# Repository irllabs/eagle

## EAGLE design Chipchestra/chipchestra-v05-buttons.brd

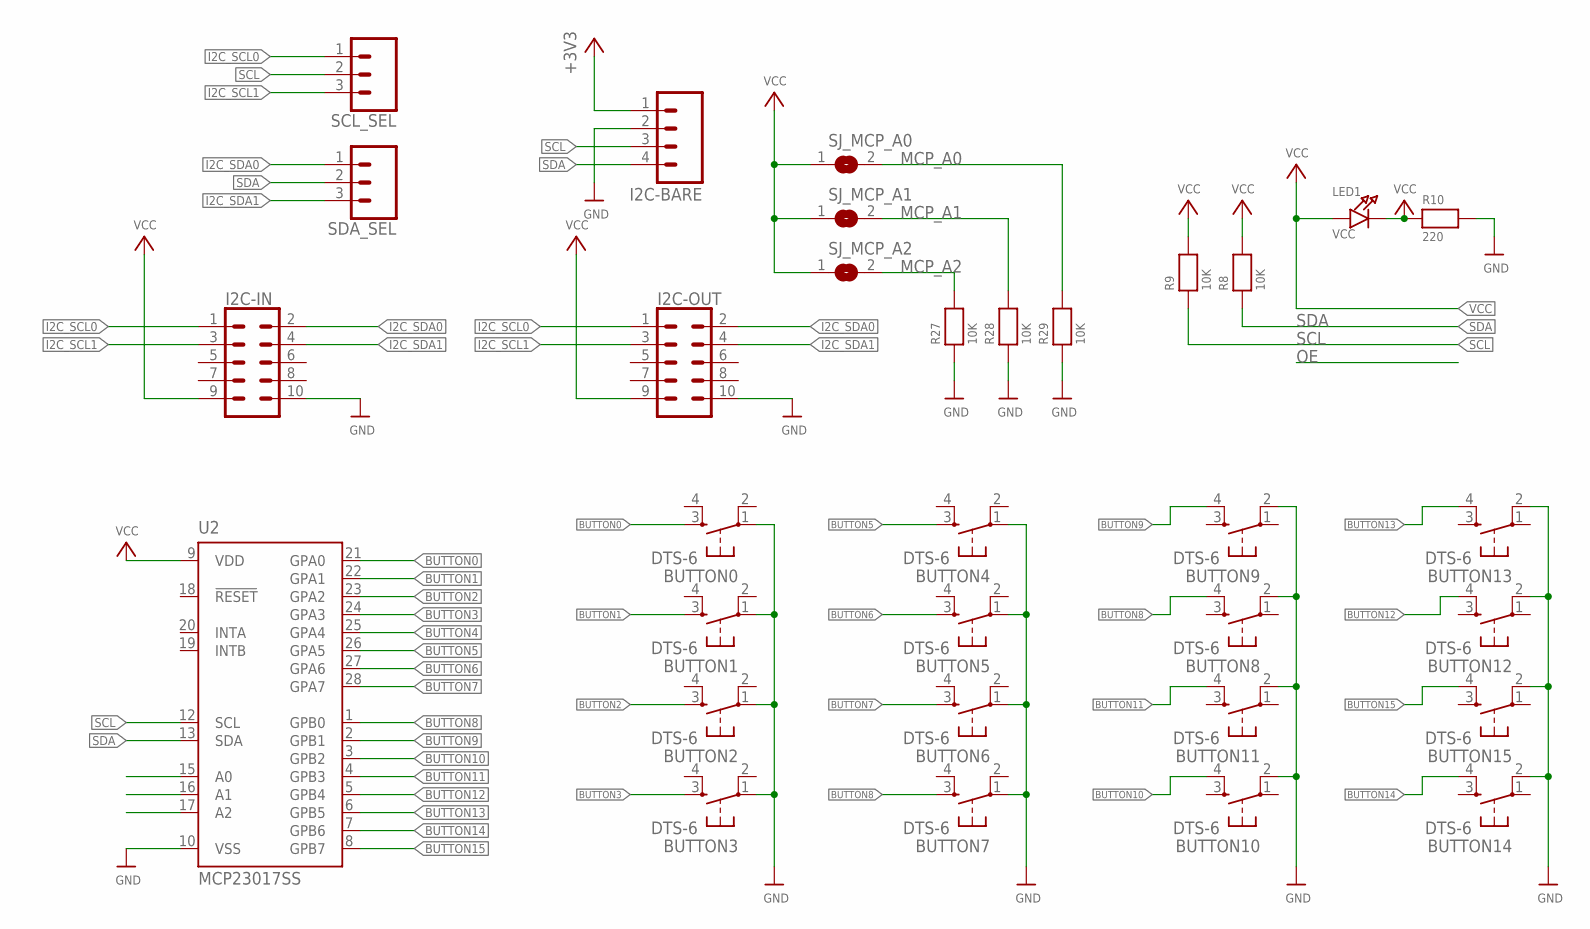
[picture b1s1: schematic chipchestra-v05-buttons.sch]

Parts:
BUTTON0, BUTTON1, BUTTON2, BUTTON3, BUTTON4, BUTTON5, BUTTON6, BUTTON7, BUTTON8, BUTTON9, BUTTON10, BUTTON11, BUTTON12, BUTTON13, BUTTON14, BUTTON15: DTS-6
I2C-BARE: M04LOCK; 1X04_LOCK
I2C-IN, I2C-OUT: CONN_05X2SHD_LOCK; 2X5-SHROUDED_LOCK
LED1: VCC; CHIPLED_0805
R8, R9, R27, R28, R29: 10K; 0805
R10: 220; 0805
SCL_SEL: CONN_03LOCK; 1X03_LOCK
SDA_SEL: CONN_03LOCK; 1X03_LOCK
SJ_MCP_A0, SJ_MCP_A1, SJ_MCP_A2: SOLDERJUMPERREFLOW_NOPASTE; SOLDERJUMPER_REFLOW_NOPASTE
U2: MCP23017SS; SSOP28

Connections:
+3V3: I2C-BARE.1
BUTTON0: BUTTON0.3, U2.21 (GPA0)
BUTTON1: BUTTON1.3, U2.22 (GPA1)
BUTTON2: BUTTON2.3, U2.23 (GPA2)
BUTTON3: BUTTON3.3, U2.24 (GPA3)
BUTTON4: U2.25 (GPA4)
BUTTON5: BUTTON4.3, U2.26 (GPA5)
BUTTON6: BUTTON5.3, U2.27 (GPA6)
BUTTON7: BUTTON6.3, U2.28 (GPA7)
BUTTON8: BUTTON7.3, BUTTON8.4, U2.1 (GPB0)
BUTTON9: BUTTON9.4, U2.2 (GPB1)
BUTTON10: BUTTON10.4, U2.3 (GPB2)
BUTTON11: BUTTON11.4, U2.4 (GPB3)
BUTTON12: BUTTON12.4, U2.5 (GPB4)
BUTTON13: BUTTON13.4, U2.6 (GPB5)
BUTTON14: BUTTON14.4, U2.7 (GPB6)
BUTTON15: BUTTON15.4, U2.8 (GPB7)
GND: BUTTON0.1, BUTTON1.1, BUTTON2.1, BUTTON3.1, BUTTON4.1, BUTTON5.1, BUTTON6.1, BUTTON7.1, BUTTON8.2, BUTTON9.2, BUTTON10.2, BUTTON11.2, BUTTON12.2, BUTTON13.2, BUTTON14.2, BUTTON15.2, I2C-BARE.2, I2C-IN.10, I2C-OUT.10, R10.2, R27.1, R28.1, R29.1, U2.10 (VSS)
I2C_SCL0: I2C-IN.1, I2C-OUT.1, SCL_SEL.1
I2C_SCL1: I2C-IN.3, I2C-OUT.3, SCL_SEL.3
I2C_SDA0: I2C-IN.2, I2C-OUT.2, SDA_SEL.1
I2C_SDA1: I2C-IN.4, I2C-OUT.4, SDA_SEL.3
MCP_A0: R29.2, SJ_MCP_A0.2, U2.15 (A0)
MCP_A1: R28.2, SJ_MCP_A1.2, U2.16 (A1)
MCP_A2: R27.2, SJ_MCP_A2.2, U2.17 (A2)
unnamed: LED1.C, R10.1
SCL: I2C-BARE.3, R9.1, SCL_SEL.2, U2.12 (SCL)
SDA: I2C-BARE.4, R8.1, SDA_SEL.2, U2.13 (SDA)
VCC: I2C-IN.9, I2C-OUT.9, LED1.A, R8.2, R9.2, SJ_MCP_A0.1, SJ_MCP_A1.1, SJ_MCP_A2.1, U2.9 (VDD)

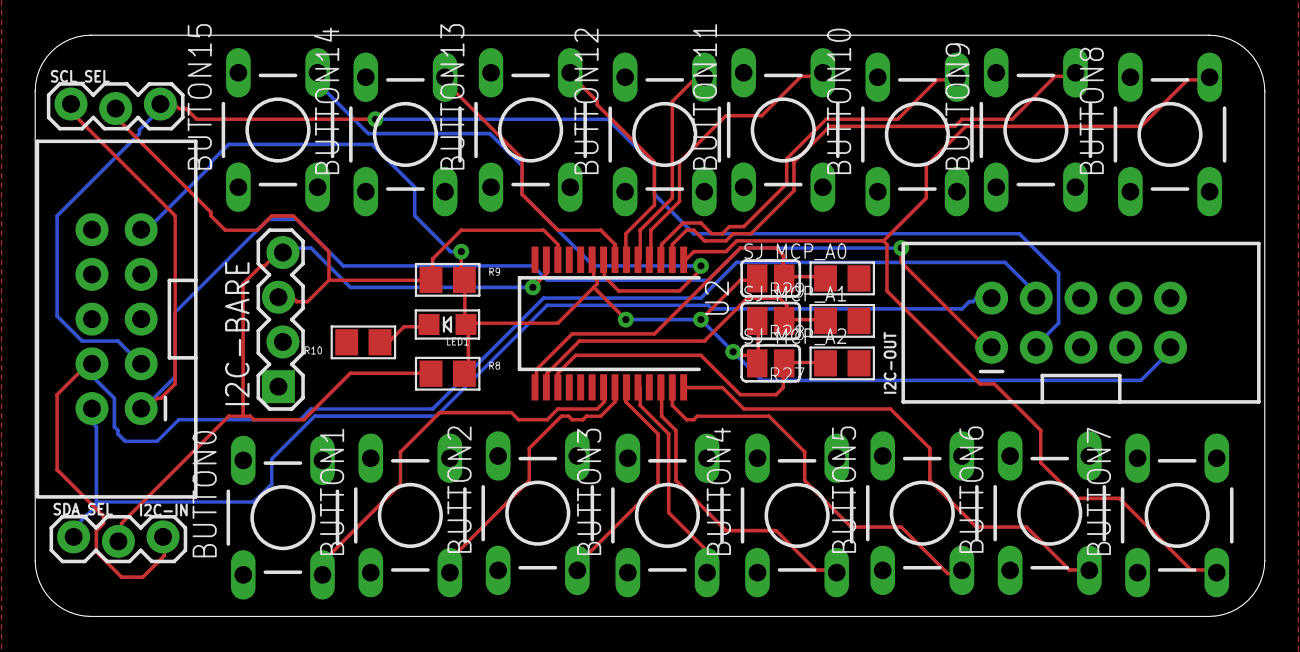
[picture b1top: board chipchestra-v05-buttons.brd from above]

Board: 2 copper layers, 69.8 x 33.0 mm, 32 parts (0 on the bottom side), 27 nets.

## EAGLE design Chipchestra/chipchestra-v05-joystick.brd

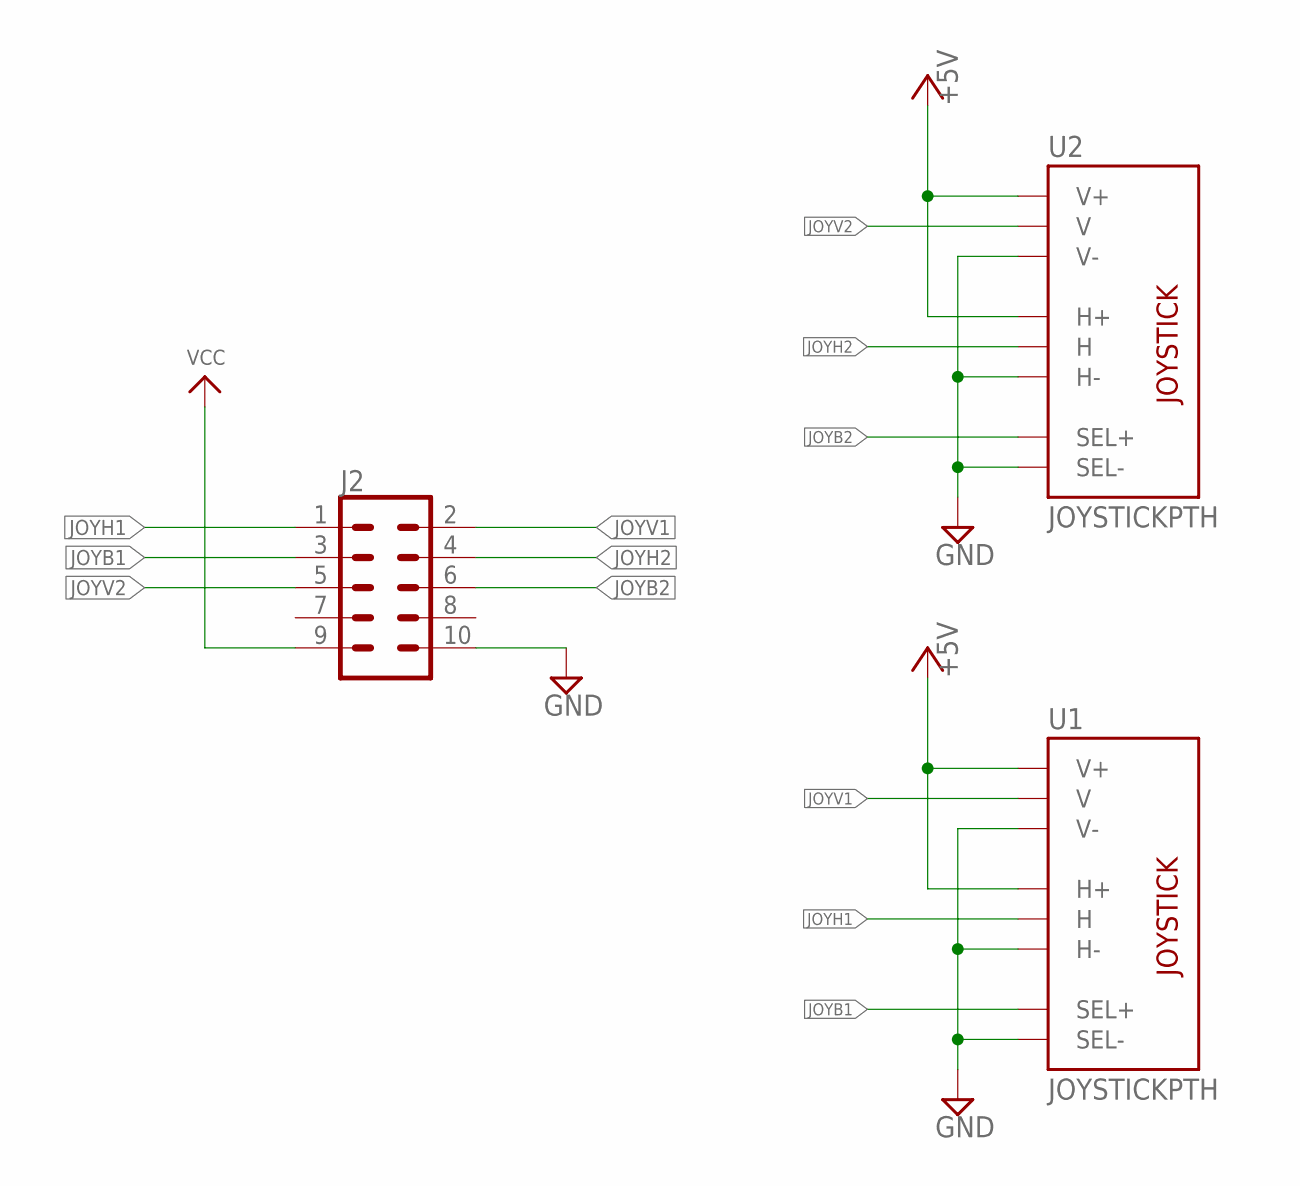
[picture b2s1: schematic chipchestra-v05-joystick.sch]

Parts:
J2: CONN_05X2SHD_LOCK; 2X5-SHROUDED_LOCK
U1, U2: JOYSTICKPTH; JOYSTICK

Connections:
+5V: U1.H1 (H+), U1.V1 (V+), U2.H1 (H+), U2.V1 (V+)
GND: J2.10, U1.B2A (SEL-), U1.H3 (H-), U1.V3 (V-), U2.B2A (SEL-), U2.H3 (H-), U2.V3 (V-)
JOYB1: J2.3, U1.B1A (SEL+)
JOYB2: J2.6, U2.B1A (SEL+)
JOYH1: J2.1, U1.H2 (H)
JOYH2: J2.4, U2.H2 (H)
JOYV1: J2.2, U1.V2 (V)
JOYV2: J2.5, U2.V2 (V)
VCC: J2.9

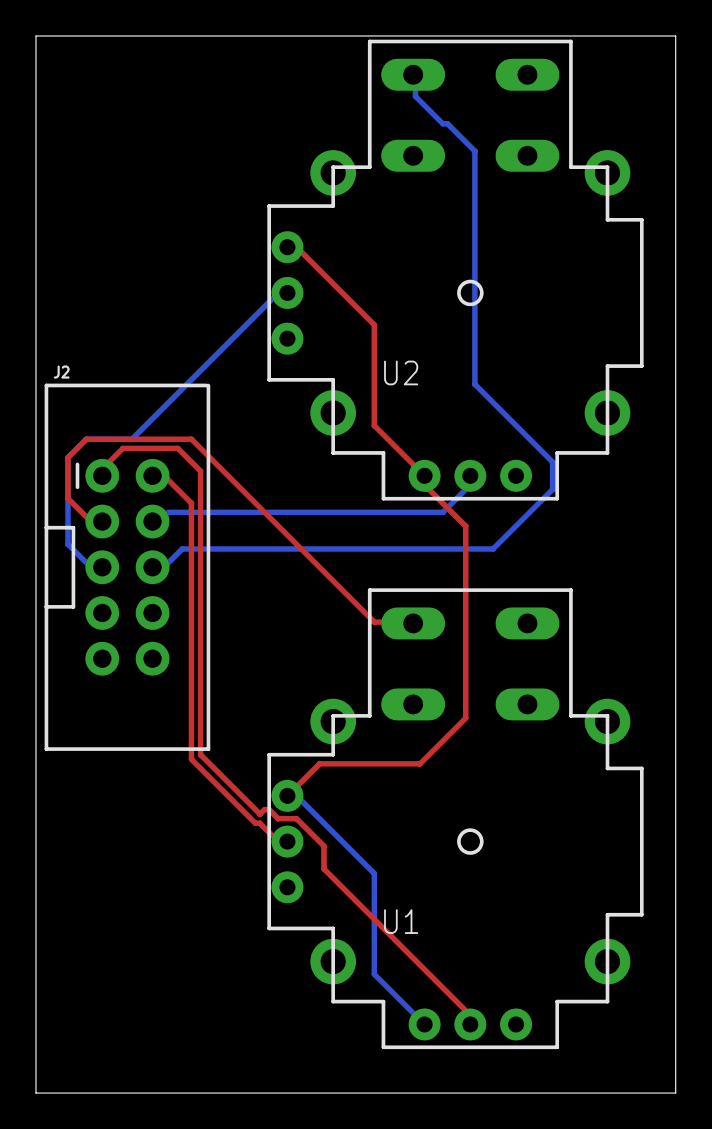
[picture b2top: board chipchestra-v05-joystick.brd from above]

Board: 2 copper layers, 35.5 x 58.7 mm, 3 parts (0 on the bottom side), 8 nets.

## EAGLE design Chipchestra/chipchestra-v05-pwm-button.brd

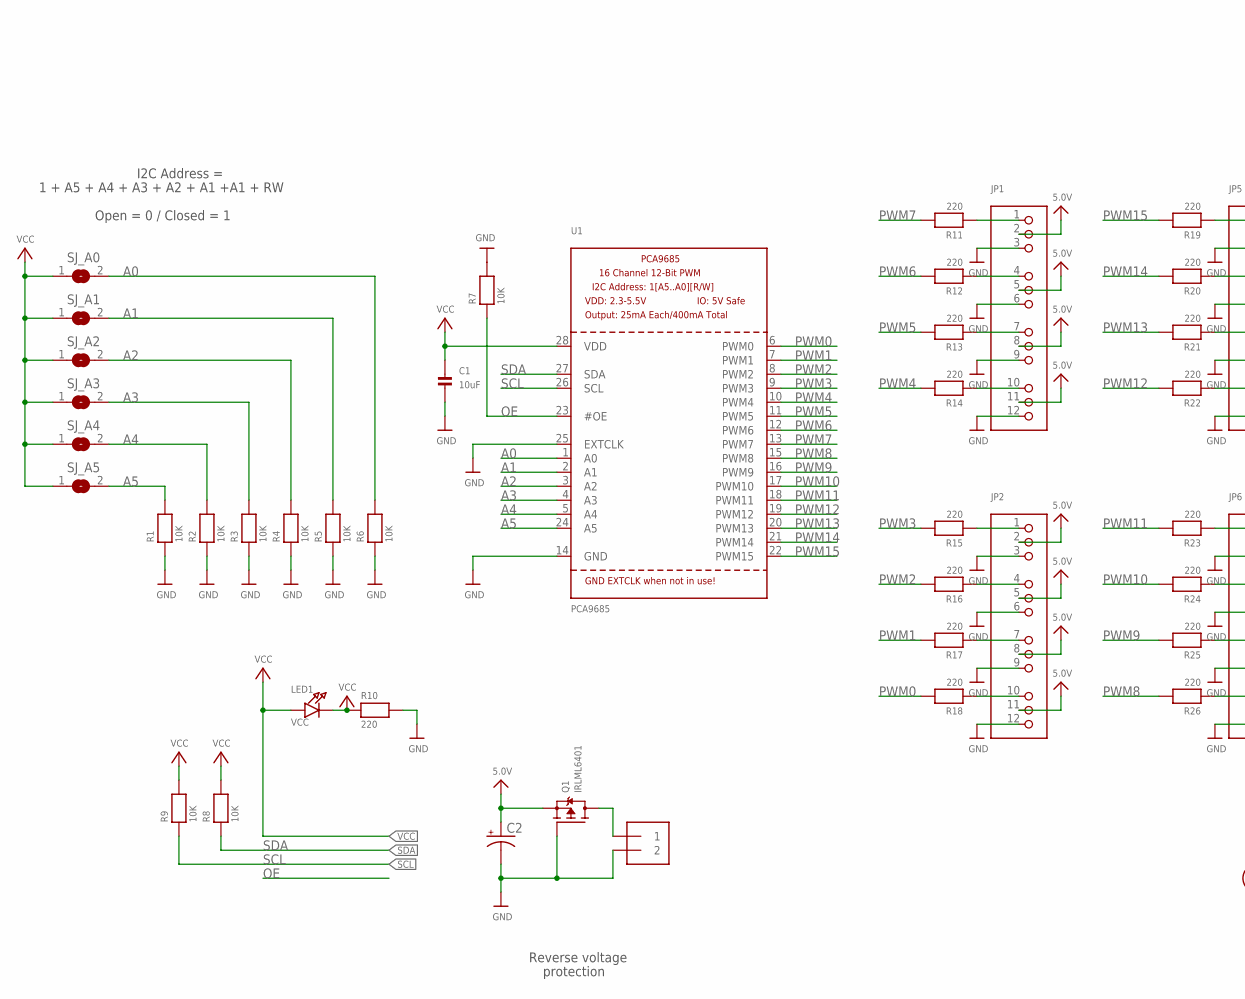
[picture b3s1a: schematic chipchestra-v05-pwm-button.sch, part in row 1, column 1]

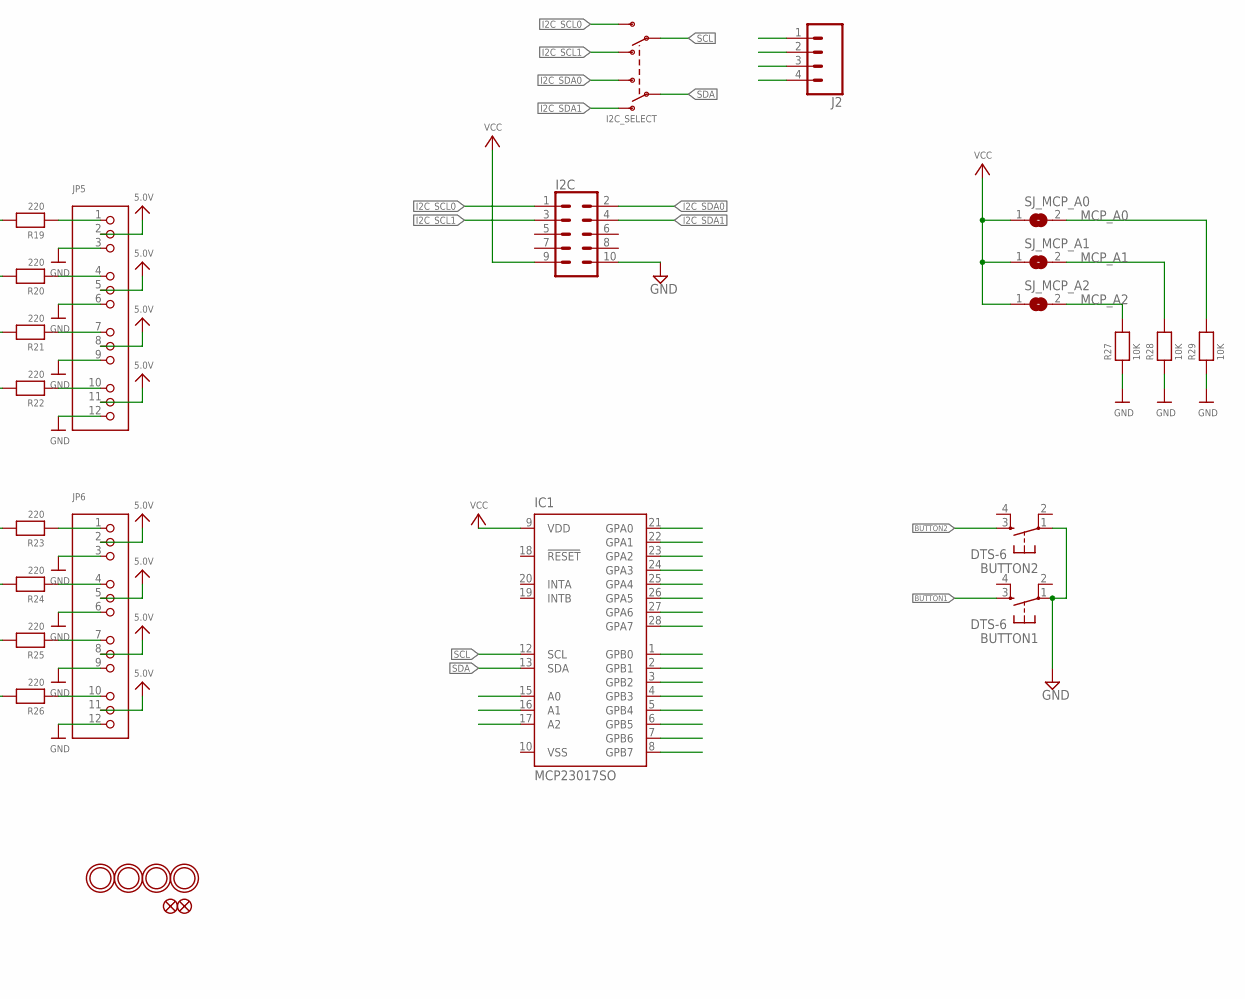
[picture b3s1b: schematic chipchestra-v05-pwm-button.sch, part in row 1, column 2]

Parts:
BUTTON1, BUTTON2: DTS-6
C1: 10uF; 0805
C2: CPOL-USE3.5-8; E3,5-8
FID1, FID2: FIDUCIAL""; FIDUCIAL_1MM
I2C: CONN_05X2SHD_LOCK; 2X5-SHROUDED_LOCK
I2C_SELECT: SWITCH_DPDT; DPDT_SMT_JS202011SCQN
IC1: MCP23017SO; SO28W
J1: TERMBLOCK_1X2-3.5MM; 1X2-3.5MM
J2: CONN_04LOCK; 1X04_LOCK
JP1, JP2, JP5, JP6: HEADER-3X04; 3X04
LED1: VCC; CHIPLED_0805
Q1: IRLML6401; SOT23-WIDE
R1, R2, R3, R4, R5, R6, R7, R8, R9, R27, R28, R29: 10K; 0805
R10, R11, R12, R13, R14, R15, R16, R17, R18, R19, R20, R21, R22, R23, R24, R25, R26: 220; 0805
SJ_A0, SJ_A1, SJ_A2, SJ_A3, SJ_A4, SJ_A5: SOLDERJUMPERREFLOW_NOPASTE; SOLDERJUMPER_REFLOW_NOPASTE
SJ_MCP_A0, SJ_MCP_A1, SJ_MCP_A2: SOLDERJUMPERREFLOW_NOPASTE; SOLDERJUMPER_REFLOW_NOPASTE
U1: PCA9685; TSSOP28
U$47, U$48, U$49, U$50: MOUNTINGHOLE2.5; MOUNTINGHOLE_2.5_PLATED

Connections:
5.0V: C2.+, JP1.2, JP1.5, JP1.8, JP1.11, JP2.2, JP2.5, JP2.8, JP2.11, JP5.2, JP5.5, JP5.8, JP5.11, JP6.2, JP6.5, JP6.8, JP6.11, Q1.2 (S)
A0: R6.2, SJ_A0.2, U1.1 (A0)
A1: R5.2, SJ_A1.2, U1.2 (A1)
A2: R4.2, SJ_A2.2, U1.3 (A2)
A3: R3.2, SJ_A3.2, U1.4 (A3)
A4: R2.2, SJ_A4.2, U1.5 (A4)
A5: R1.2, SJ_A5.2, U1.24 (A5)
BUTTON0: IC1.21 (GPA0)
BUTTON1: BUTTON1.3, IC1.22 (GPA1)
BUTTON2: BUTTON2.3, IC1.23 (GPA2)
BUTTON3: IC1.24 (GPA3)
BUTTON4: IC1.25 (GPA4)
BUTTON5: IC1.26 (GPA5)
BUTTON6: IC1.27 (GPA6)
BUTTON7: IC1.28 (GPA7)
BUTTON8: IC1.1 (GPB0)
BUTTON9: IC1.2 (GPB1)
BUTTON10: IC1.3 (GPB2)
BUTTON11: IC1.4 (GPB3)
BUTTON12: IC1.5 (GPB4)
BUTTON13: IC1.6 (GPB5)
BUTTON14: IC1.7 (GPB6)
BUTTON15: IC1.8 (GPB7)
GND: BUTTON1.1, BUTTON2.1, C1.2, C2.-, I2C.10, J1.2, JP1.3, JP1.6, JP1.9, JP1.12, JP2.3, JP2.6, JP2.9, JP2.12, JP5.3, JP5.6, JP5.9, JP5.12, JP6.3, JP6.6, JP6.9, JP6.12, Q1.1 (G), R1.1, R2.1, R3.1, R4.1, R5.1, R6.1, R7.2, R10.2, R27.1, R28.1, R29.1, U1.14 (GND), U1.25 (EXTCLK)
I2C_SCL0: I2C.1, I2C_SELECT.P$4 (S2)
I2C_SCL1: I2C.3, I2C_SELECT.P$6 (O2)
I2C_SDA0: I2C.2, I2C_SELECT.P$3 (S1)
I2C_SDA1: I2C.4, I2C_SELECT.P$1 (O1)
MCP_A0: IC1.15 (A0), R29.2, SJ_MCP_A0.2
MCP_A1: IC1.16 (A1), R28.2, SJ_MCP_A1.2
MCP_A2: IC1.17 (A2), R27.2, SJ_MCP_A2.2
unnamed: LED1.C, R10.1
unnamed: JP1.4, R12.1
unnamed: JP1.1, R11.1
unnamed: JP1.7, R13.1
unnamed: JP1.10, R14.1
unnamed: JP2.1, R15.1
unnamed: JP2.4, R16.1
unnamed: JP2.7, R17.1
unnamed: JP2.10, R18.1
unnamed: JP6.10, R26.1
unnamed: JP6.7, R25.1
unnamed: JP6.4, R24.1
unnamed: JP6.1, R23.1
unnamed: JP5.10, R22.1
unnamed: JP5.7, R21.1
unnamed: JP5.4, R20.1
unnamed: JP5.1, R19.1
OE: R7.1, U1.23 (#OE)
PWM0: R18.2, U1.6 (PWM0)
PWM1: R17.2, U1.7 (PWM1)
PWM2: R16.2, U1.8 (PWM2)
PWM3: R15.2, U1.9 (PWM3)
PWM4: R14.2, U1.10 (PWM4)
PWM5: R13.2, U1.11 (PWM5)
PWM6: R12.2, U1.12 (PWM6)
PWM7: R11.2, U1.13 (PWM7)
PWM8: R26.2, U1.15 (PWM8)
PWM9: R25.2, U1.16 (PWM9)
PWM10: R24.2, U1.17 (PWM10)
PWM11: R23.2, U1.18 (PWM11)
PWM12: R22.2, U1.19 (PWM12)
PWM13: R21.2, U1.20 (PWM13)
PWM14: R20.2, U1.21 (PWM14)
PWM15: R19.2, U1.22 (PWM15)
PWRIN: J1.1, Q1.3 (D)
SCL: I2C_SELECT.P$5 (P2), IC1.12 (SCL), R9.1, U1.26 (SCL)
SDA: I2C_SELECT.P$2 (P1), IC1.13 (SDA), R8.1, U1.27 (SDA)
VCC: C1.1, I2C.9, IC1.9 (VDD), LED1.A, R8.2, R9.2, SJ_A0.1, SJ_A1.1, SJ_A2.1, SJ_A3.1, SJ_A4.1, SJ_A5.1, SJ_MCP_A0.1, SJ_MCP_A1.1, SJ_MCP_A2.1, U1.28 (VDD)
VSS: IC1.10 (VSS)

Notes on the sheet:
Reverse voltage
protection
1 + A5 + A4 + A3 + A2 + A1 +A1 + RW
I2C Address =
Open = 0 / Closed = 1

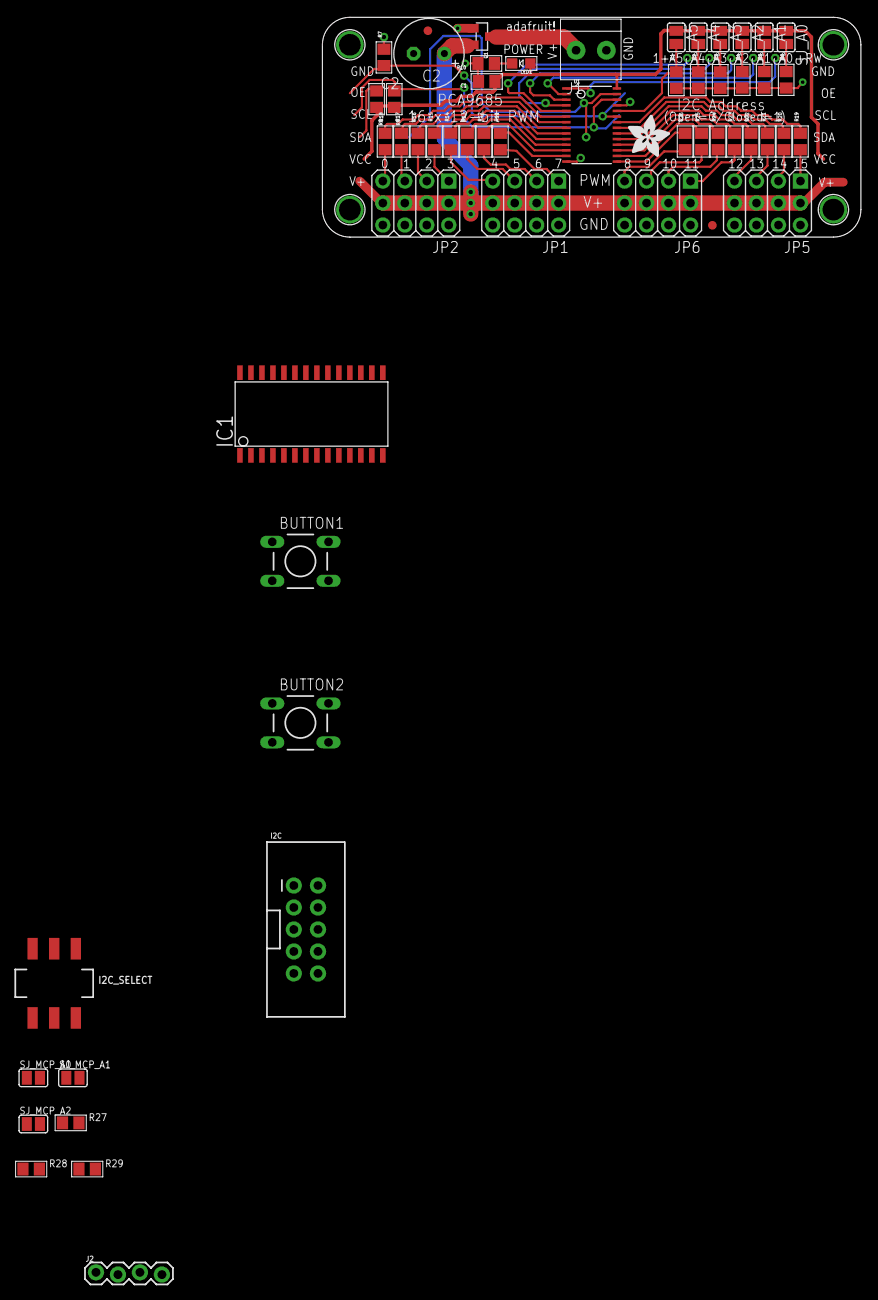
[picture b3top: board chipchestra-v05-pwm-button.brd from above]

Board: 2 copper layers, 62.2 x 25.4 mm, 61 parts (0 on the bottom side), 55 nets.

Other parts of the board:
U$51: ADAFRUIT_5MM

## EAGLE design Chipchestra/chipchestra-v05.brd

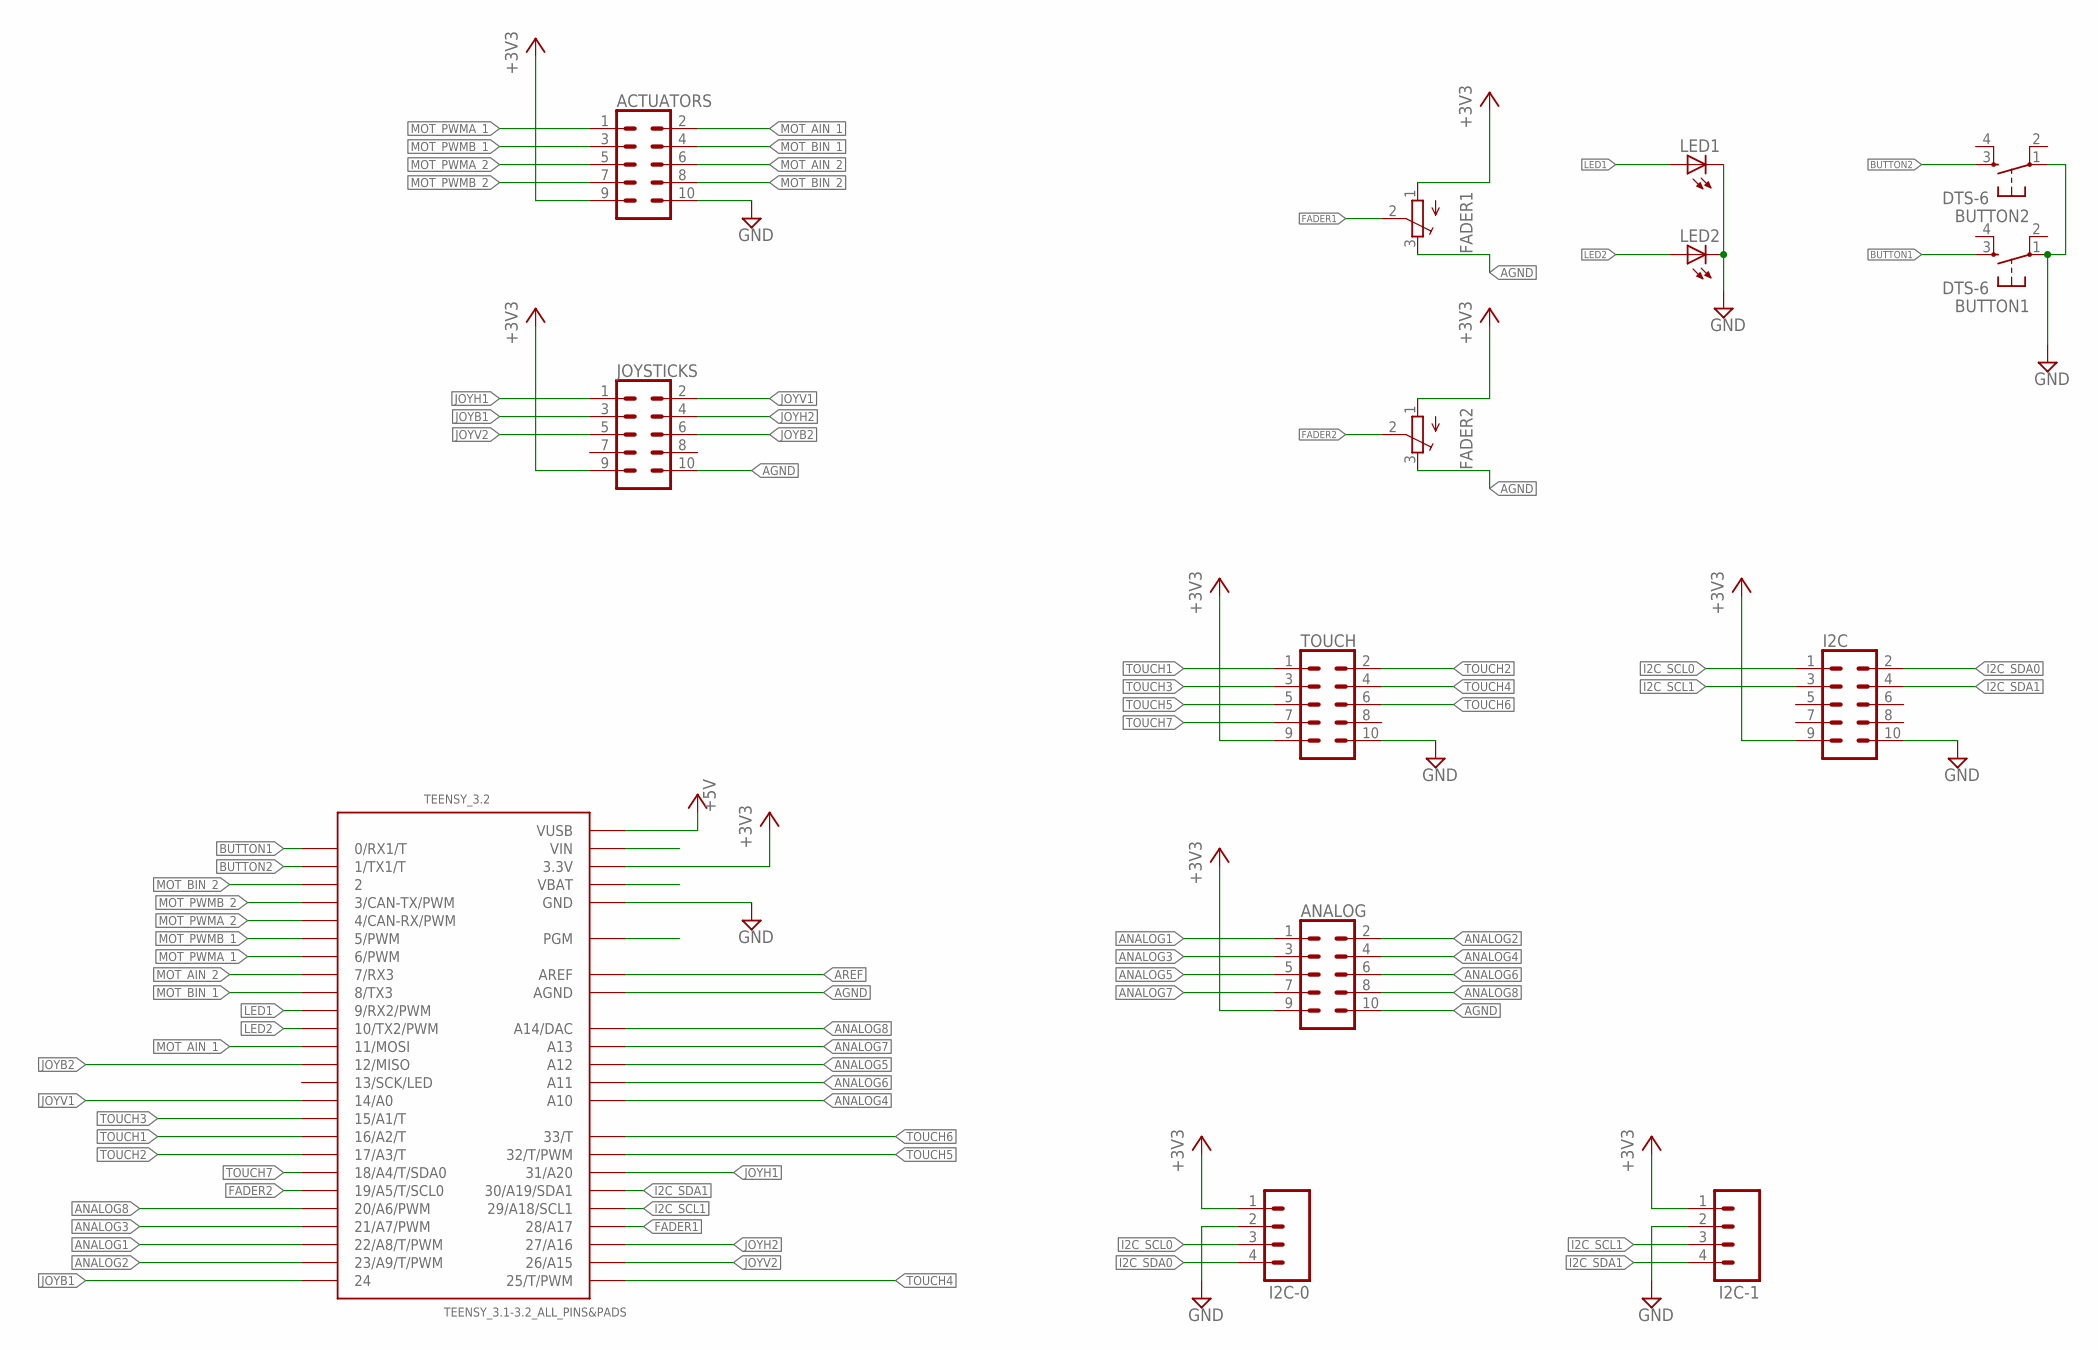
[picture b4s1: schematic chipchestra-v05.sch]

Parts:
ACTUATORS: CONN_05X2SHD_LOCK; 2X5-SHROUDED_LOCK
ANALOG: CONN_05X2SHD_LOCK; 2X5-SHROUDED_LOCK
BUTTON1, BUTTON2: DTS-6
FADER1, FADER2: TRIMPOT3386; TRIM-3386
I2C: CONN_05X2SHD_LOCK; 2X5-SHROUDED_LOCK
I2C-0, I2C-1: M04LOCK; 1X04_LOCK
JOYSTICKS: CONN_05X2SHD_LOCK; 2X5-SHROUDED_LOCK
LED1, LED2: LED3MM
TEENSY_3.2: TEENSY_3.1-3.2_ALL_PINS&PADS; TEENSY_3.0-3.2_ALL_PINS_&_PADS
TOUCH: CONN_05X2SHD_LOCK; 2X5-SHROUDED_LOCK

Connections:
+3V3: ACTUATORS.9, ANALOG.9, FADER1.1 (A), FADER2.1 (A), I2C.9, I2C-0.1, I2C-1.1, JOYSTICKS.9, TEENSY_3.2.3.3V, TEENSY_3.2.3.3V1 (3.3V), TEENSY_3.2.3.3V2 (3.3V), TOUCH.9
+5V: TEENSY_3.2.VUSB
AGND: ANALOG.10, FADER1.3 (E), FADER2.3 (E), JOYSTICKS.10, TEENSY_3.2.AGND
ANALOG1: ANALOG.1, TEENSY_3.2.22/A8 (22/A8/T/PWM)
ANALOG2: ANALOG.2, TEENSY_3.2.23/A9 (23/A9/T/PWM)
ANALOG3: ANALOG.3, TEENSY_3.2.21/A7 (21/A7/PWM)
ANALOG4: ANALOG.4, TEENSY_3.2.A10
ANALOG5: ANALOG.5, TEENSY_3.2.A12
ANALOG6: ANALOG.6, TEENSY_3.2.A11
ANALOG7: ANALOG.7, TEENSY_3.2.A13
ANALOG8: ANALOG.8, TEENSY_3.2.20/A6 (20/A6/PWM), TEENSY_3.2.RESET/DAC (A14/DAC)
AREF: TEENSY_3.2.AREF
BUTTON1: BUTTON1.3, TEENSY_3.2.0 (0/RX1/T)
BUTTON2: BUTTON2.3, TEENSY_3.2.1 (1/TX1/T)
FADER1: FADER1.2 (S), TEENSY_3.2.28 (28/A17)
FADER2: FADER2.2 (S), TEENSY_3.2.19/A5 (19/A5/T/SCL0)
GND: ACTUATORS.10, BUTTON1.1, BUTTON2.1, I2C.10, I2C-0.2, I2C-1.2, LED1.K (C), LED2.K (C), TEENSY_3.2.GND, TEENSY_3.2.GND1 (GND), TEENSY_3.2.GND2 (GND), TOUCH.10
I2C_SCL0: I2C.1, I2C-0.3
I2C_SCL1: I2C.3, I2C-1.3, TEENSY_3.2.29 (29/A18/SCL1)
I2C_SDA0: I2C.2, I2C-0.4
I2C_SDA1: I2C.4, I2C-1.4, TEENSY_3.2.30 (30/A19/SDA1)
JOYB1: JOYSTICKS.3, TEENSY_3.2.24
JOYB2: JOYSTICKS.6, TEENSY_3.2.12 (12/MISO)
JOYH1: JOYSTICKS.1, TEENSY_3.2.31 (31/A20)
JOYH2: JOYSTICKS.4, TEENSY_3.2.27 (27/A16)
JOYV1: JOYSTICKS.2, TEENSY_3.2.14/A0
JOYV2: JOYSTICKS.5, TEENSY_3.2.26 (26/A15)
LED1: LED1.A, TEENSY_3.2.9 (9/RX2/PWM)
LED2: LED2.A, TEENSY_3.2.10 (10/TX2/PWM)
MOT_AIN_1: ACTUATORS.2, TEENSY_3.2.11 (11/MOSI)
MOT_AIN_2: ACTUATORS.6, TEENSY_3.2.7 (7/RX3)
MOT_BIN_1: ACTUATORS.4, TEENSY_3.2.8 (8/TX3)
MOT_BIN_2: ACTUATORS.8, TEENSY_3.2.2
MOT_PWMA_1: ACTUATORS.1, TEENSY_3.2.6 (6/PWM)
MOT_PWMA_2: ACTUATORS.5, TEENSY_3.2.4 (4/CAN-RX/PWM)
MOT_PWMB_1: ACTUATORS.3, TEENSY_3.2.5 (5/PWM)
MOT_PWMB_2: ACTUATORS.7, TEENSY_3.2.3 (3/CAN-TX/PWM)
TOUCH1: TEENSY_3.2.16/A2 (16/A2/T), TOUCH.1
TOUCH2: TEENSY_3.2.17/A3 (17/A3/T), TOUCH.2
TOUCH3: TEENSY_3.2.15/A1 (15/A1/T), TOUCH.3
TOUCH4: TEENSY_3.2.25 (25/T/PWM), TOUCH.4
TOUCH5: TEENSY_3.2.32 (32/T/PWM), TOUCH.5
TOUCH6: TEENSY_3.2.33 (33/T), TOUCH.6
TOUCH7: TEENSY_3.2.18/A4 (18/A4/T/SDA0), TOUCH.7

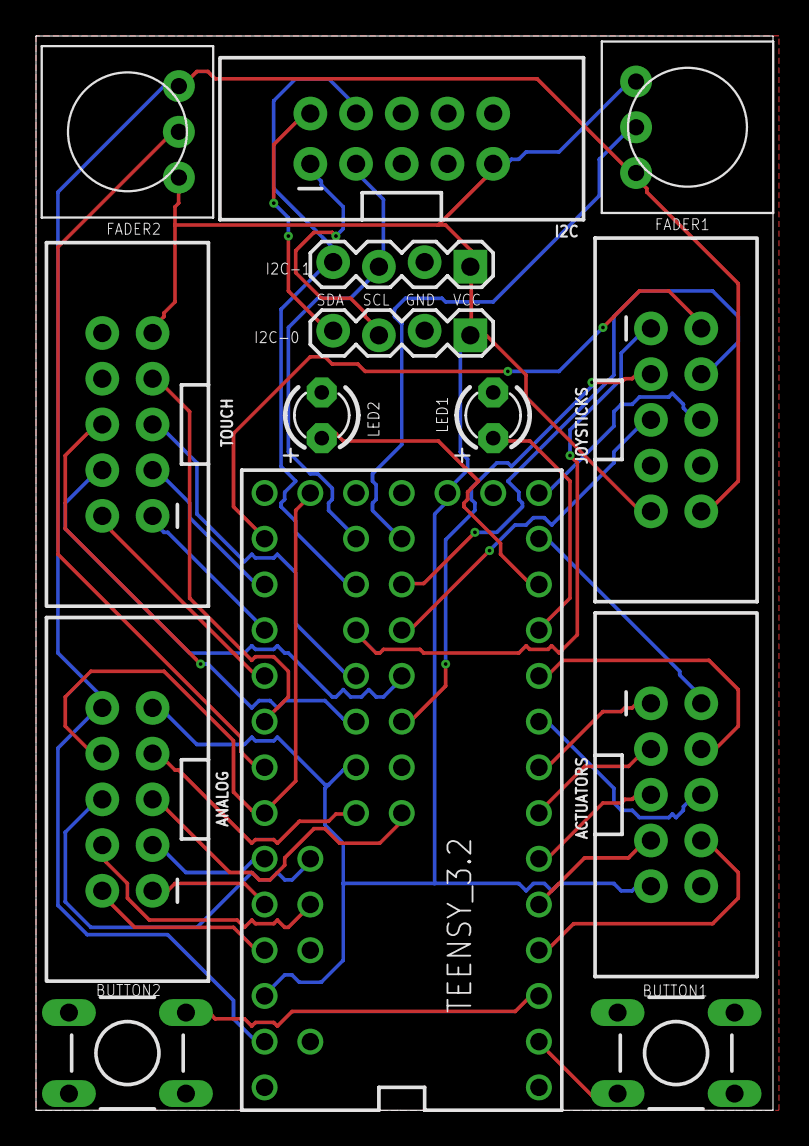
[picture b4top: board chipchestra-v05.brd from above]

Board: 2 copper layers, 40.9 x 59.7 mm, 14 parts (0 on the bottom side), 42 nets.

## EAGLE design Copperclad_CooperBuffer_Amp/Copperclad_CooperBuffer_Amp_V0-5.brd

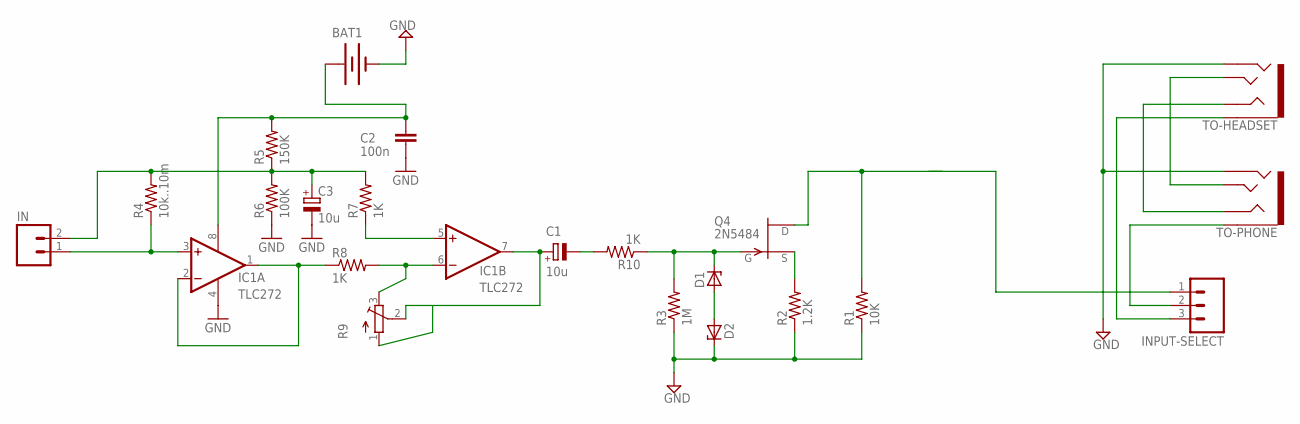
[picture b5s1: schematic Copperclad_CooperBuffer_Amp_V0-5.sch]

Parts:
BAT1: BATTERYA23; BATTERY-A23
C1, C3: 10u; E2,5-5
C2: 100n; C025-025X050
D1, D2: 1N821; DO35Z10
IC1: TLC272; DIL08
IN: M02LOCK; 1X02_LOCK
INPUT-SELECT: M03LOCK; 1X03_LOCK
Q4: 2N5484; TO92-
R1: 10K; 0204V
R2: 1.2K; 0204V
R3: 1M; 0204V
R4: 10k..10m; 0204V
R5: 150K; 0204V
R6: 100K; 0204V
R7, R8, R10: 1K; 0204V
R9: TRIMPOT3386; TRIM-3386
TO-HEADSET: AUDIO-JACK3; AUDIO-JACK-TRRS-SMD
TO-PHONE: AUDIO-JACK3; AUDIO-JACK-TRRS-SMD

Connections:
GND: BAT1.GND@1 (-), C2.1, C3.-, D2.C, IC1.4 (V-), R1.1, R2.1, R3.1, R6.1, TO-HEADSET.RING2, TO-PHONE.RING2
unnamed: D1.A, D2.A
unnamed: Q4.2 (S), R2.2
unnamed: IC1.5 (+IN), R7.1
unnamed: C1.+, IC1.7 (OUT), R9.1 (A), R9.2 (S)
unnamed: IC1.6 (-IN), R8.2, R9.3 (E)
unnamed: C3.+, IN.2, R4.2, R5.1, R6.2, R7.2
unnamed: IC1.3 (+IN), IN.1, R4.1
unnamed: D1.C, Q4.1 (G), R3.2, R10.1
unnamed: C1.-, R10.2
unnamed: INPUT-SELECT.3, TO-HEADSET.EARTH
unnamed: TO-HEADSET.TIP, TO-PHONE.TIP
unnamed: IC1.1 (OUT), IC1.2 (-IN), R8.1
unnamed: TO-HEADSET.RING1, TO-PHONE.RING1
TO-PHONE: INPUT-SELECT.2, TO-PHONE.EARTH
V9V: BAT1.PWR@1 (+), C2.2, IC1.8 (V+), R5.2
`DEL: INPUT-SELECT.1, Q4.3 (D), R1.2

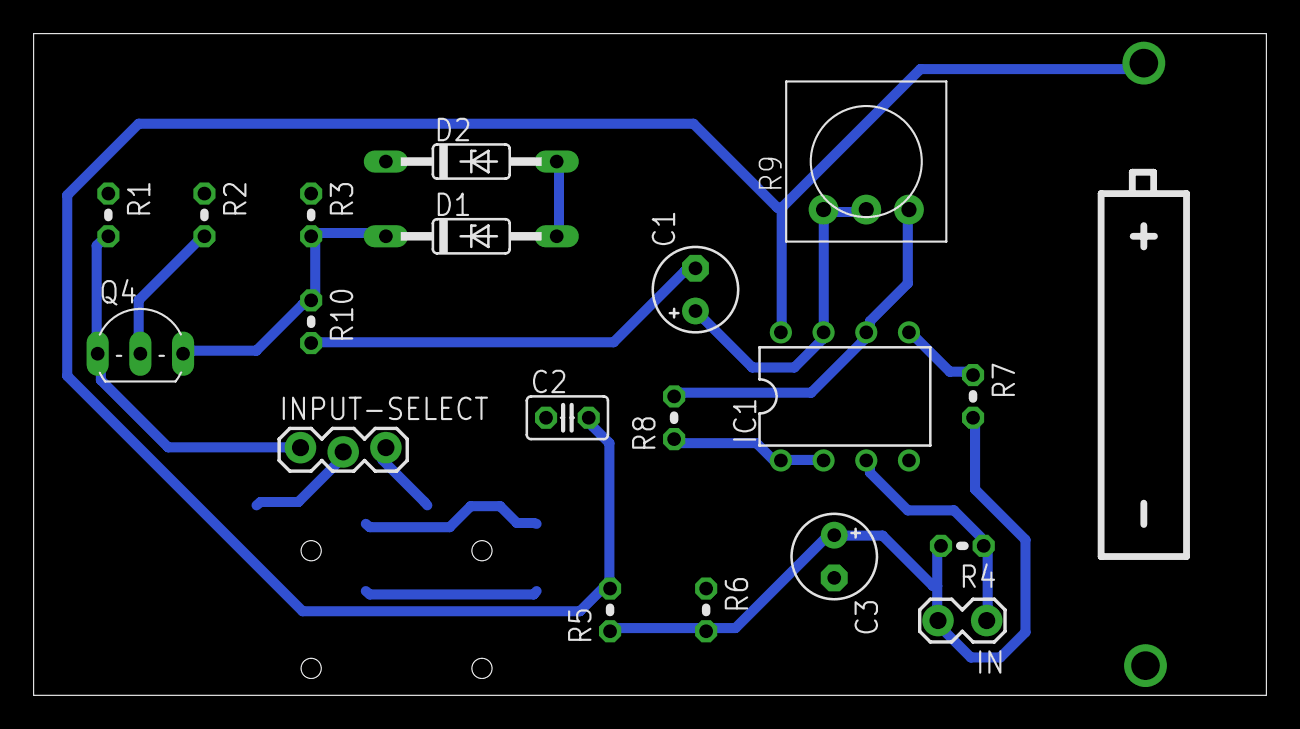
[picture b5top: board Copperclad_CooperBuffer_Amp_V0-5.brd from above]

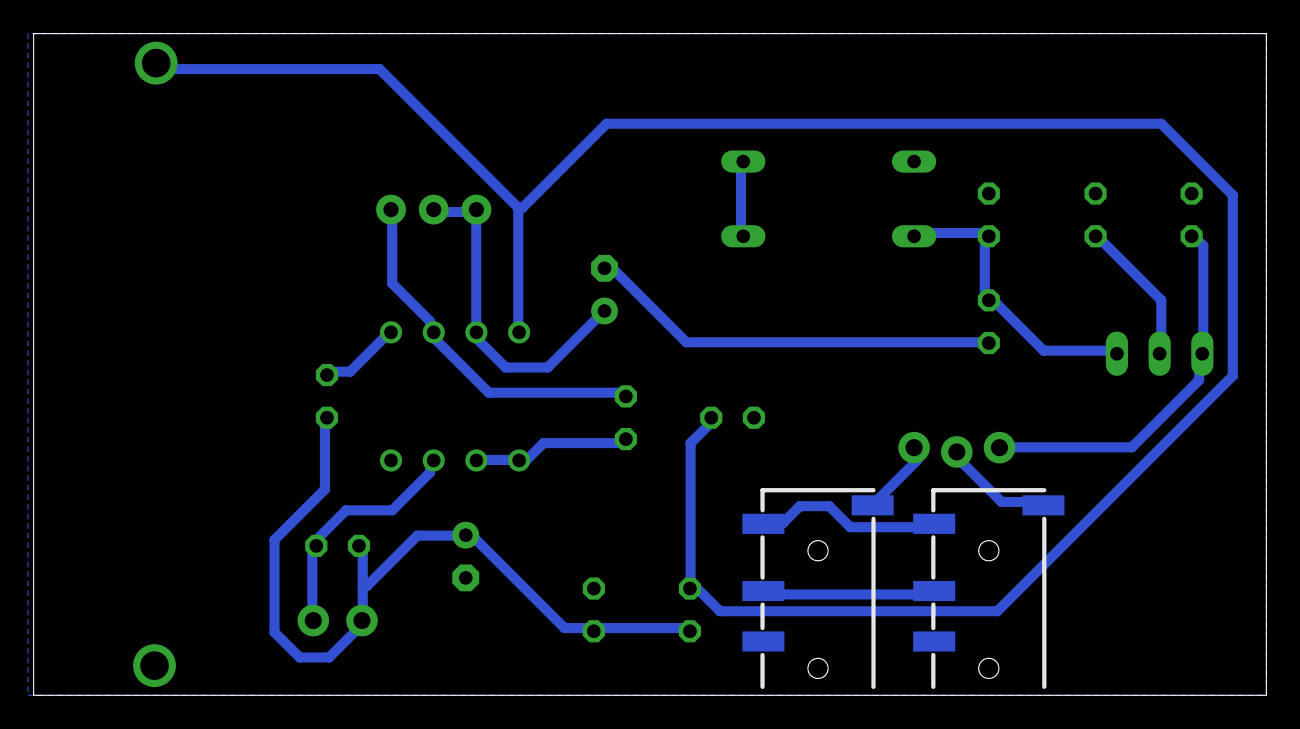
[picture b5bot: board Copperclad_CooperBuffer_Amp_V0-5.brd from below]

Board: 2 copper layers, 73.3 x 39.4 mm, 22 parts (2 on the bottom side), 17 nets.

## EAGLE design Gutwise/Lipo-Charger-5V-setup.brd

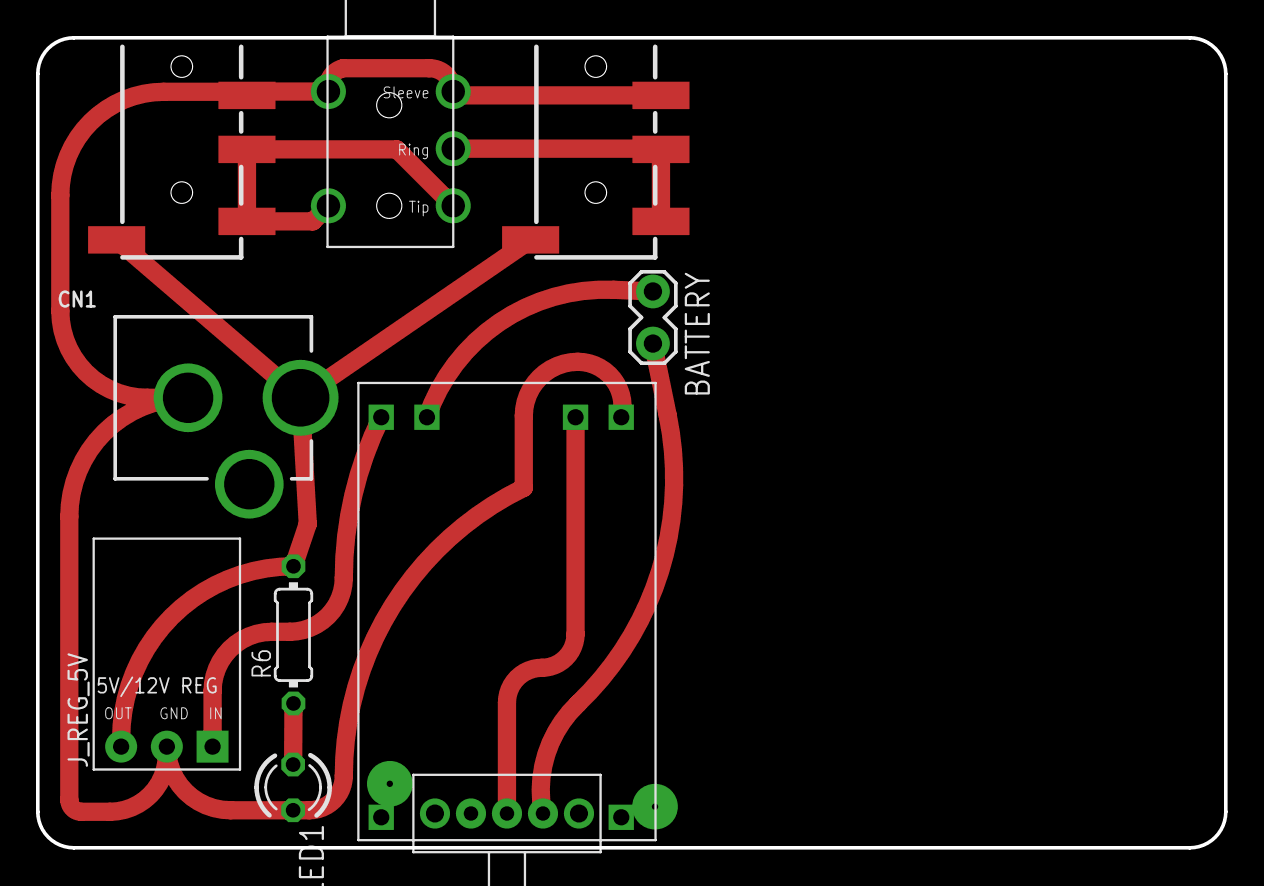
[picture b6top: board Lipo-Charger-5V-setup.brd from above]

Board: 2 copper layers, 66.0 x 45.0 mm, 10 parts (0 on the bottom side), 9 nets.

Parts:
AUDIO_OUT: 1/8"-F-STEREO-PCB
BATTERY: 1X02_LOCK
CN1: DCJACK_2MM_PTH
J_REG_5V: POLOLU_VOLTAGE_REGULATORS_3PIN; POLOLU_5V-12V_STEPUP_U3V12F5-U3V12F12
LED1: LED3MM
POWER: SPDT; SWITCH_SPDT-TE-CONNECT
R6: 390; 0204/7
U$4, U$5: AUDIO-JACK3LGPADS; AUDIO-JACK-TRRS-SMD
USB-LIPO-CHARGER: TP4056-MODULE; TP4056-LITHIUM-PROTECTED-MODULE

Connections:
+5V: CN1.PWR, J_REG_5V.VOUT, R6.2, U$4.EARTH, U$5.EARTH
GND: AUDIO_OUT.SLEEVE1, AUDIO_OUT.SLEEVE2, CN1.GND, J_REG_5V.GND, LED1.K, U$4.RING2, U$5.RING2, USB-LIPO-CHARGER.OUT-
unnamed: BATTERY.2, POWER.3
unnamed: LED1.A, R6.1
unnamed: AUDIO_OUT.RING, U$5.RING1, U$5.TIP
unnamed: BATTERY.1, USB-LIPO-CHARGER.B+
unnamed: POWER.2, USB-LIPO-CHARGER.B-
OUT2: AUDIO_OUT.TIP1, AUDIO_OUT.TIP2, U$4.RING1, U$4.TIP
VIN: J_REG_5V.VIN, USB-LIPO-CHARGER.OUT+

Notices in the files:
parts and their libraries:
SparkFun-Connectors: Licensing: Creative Commons ShareAlike 4.0 International - https://creativecommons.org/licenses/by-sa/4.0
microbuilder: This work is placed in the public domain, and may be freely used for commercial and non-commercial work with the following conditions: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
